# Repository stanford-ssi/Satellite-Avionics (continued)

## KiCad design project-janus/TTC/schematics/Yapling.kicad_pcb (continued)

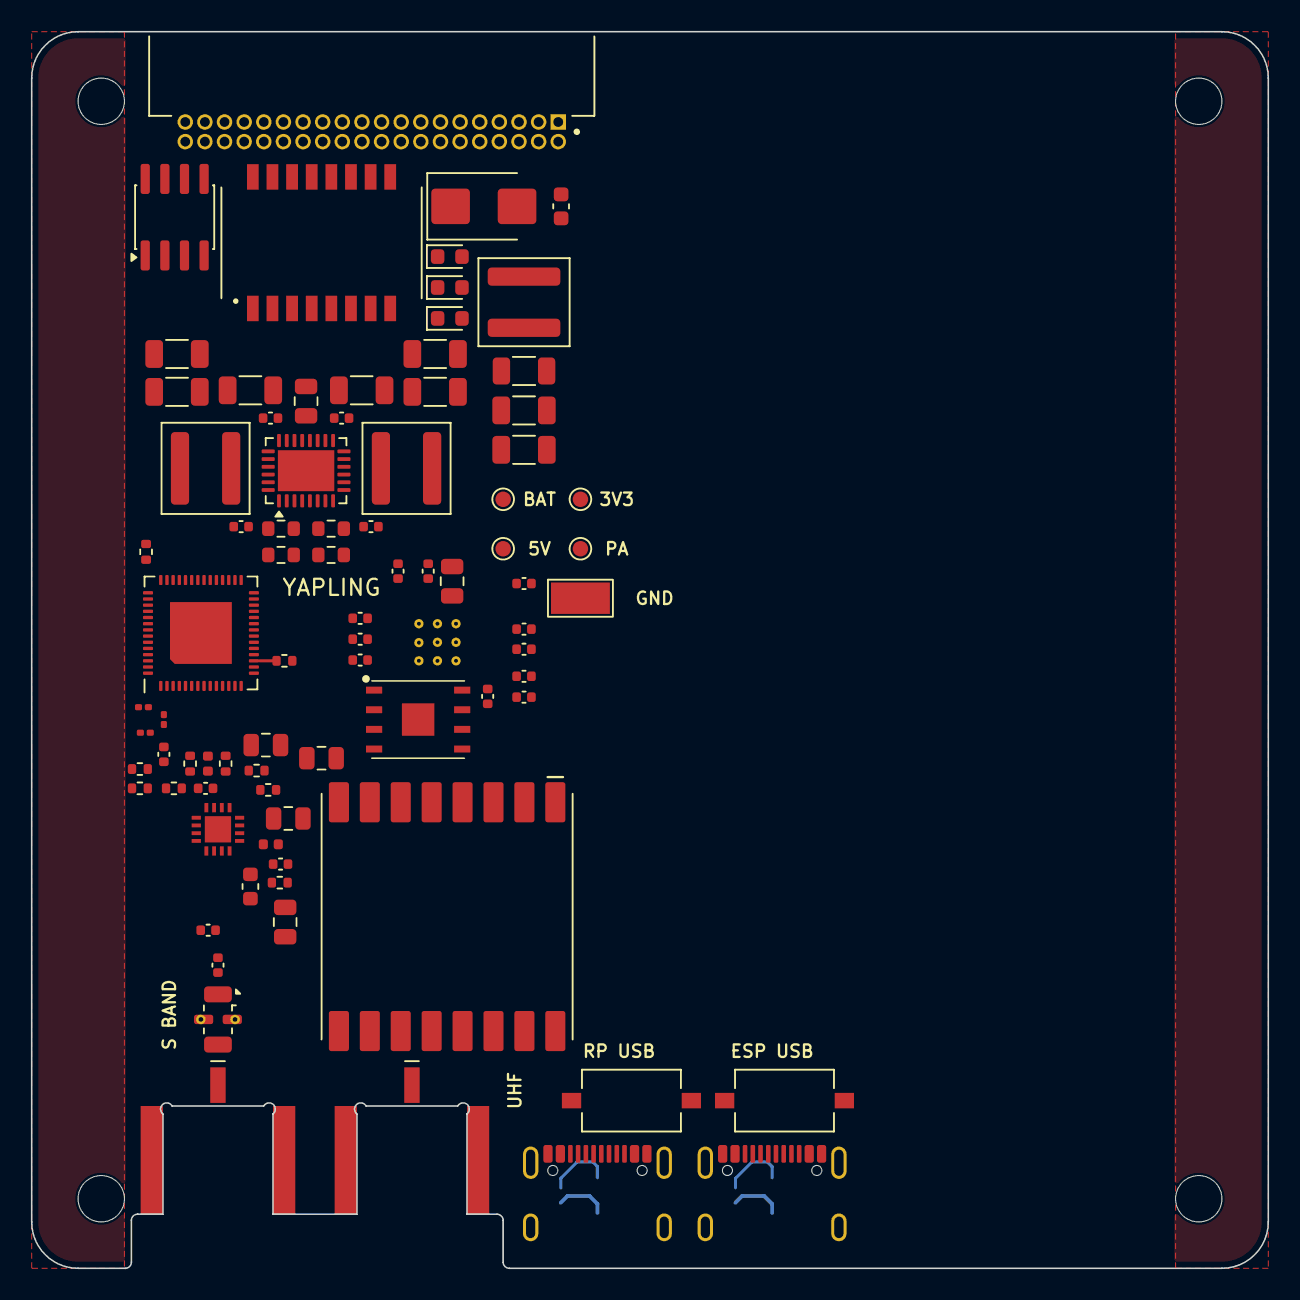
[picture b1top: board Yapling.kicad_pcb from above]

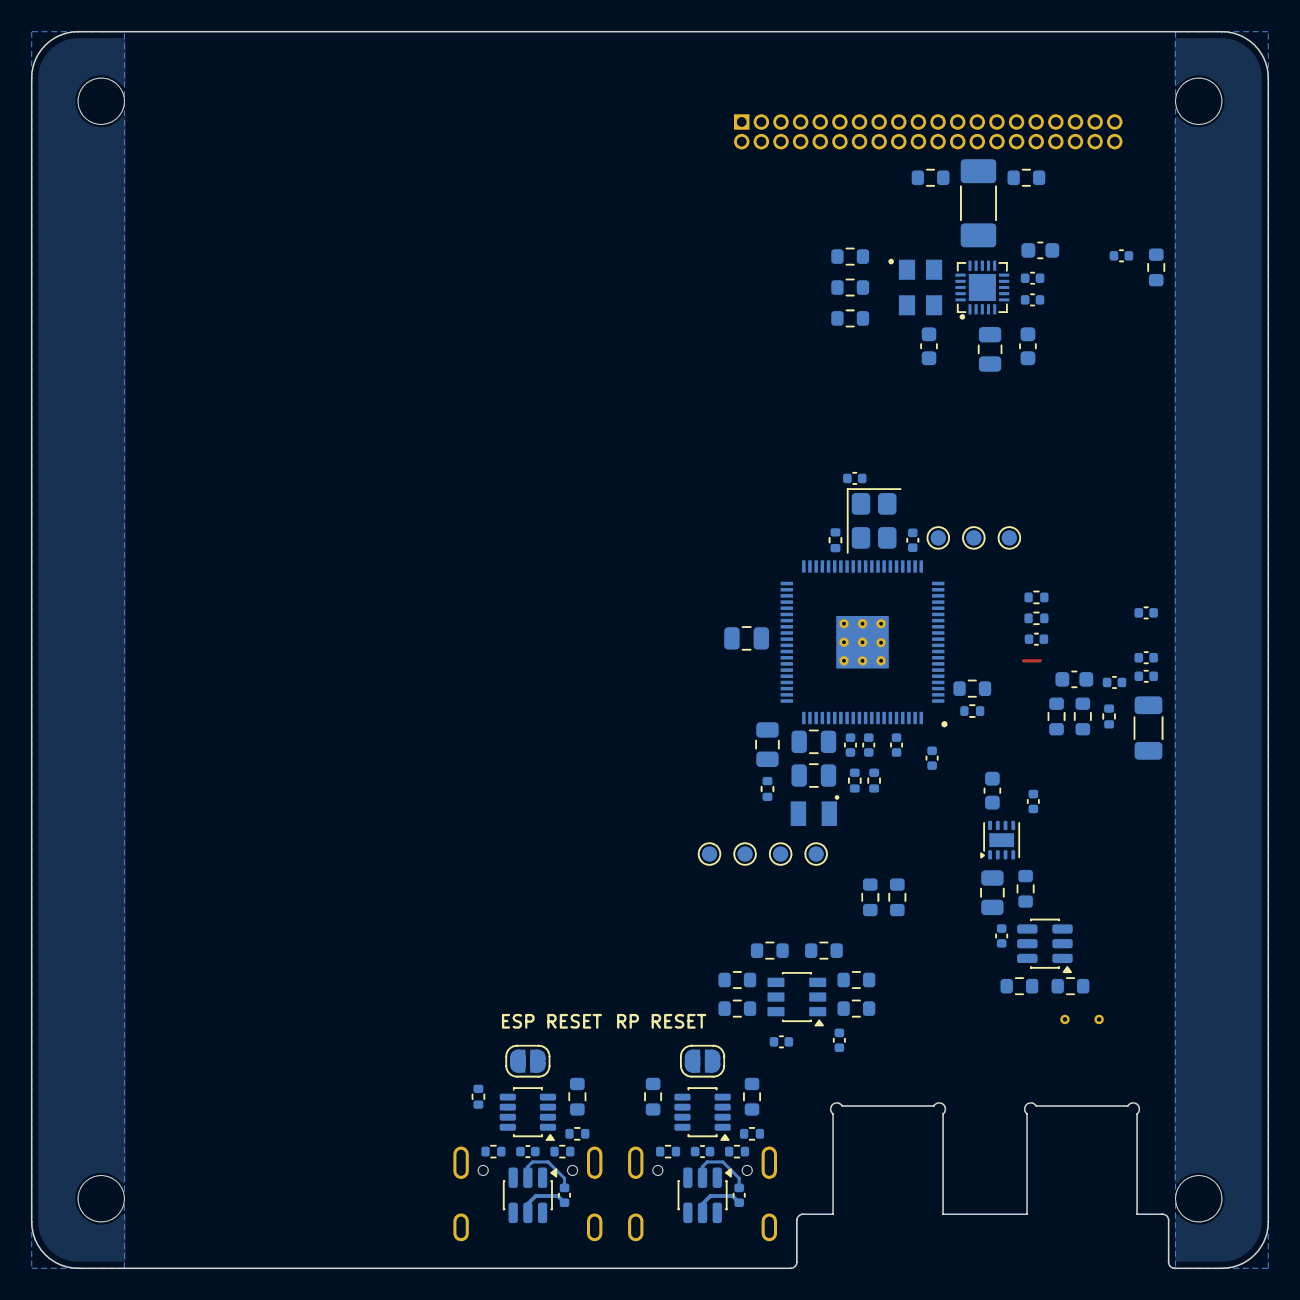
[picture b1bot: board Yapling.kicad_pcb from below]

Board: 4 copper layers, 80.0 x 80.0 mm, 182 parts (94 on the bottom side), 123 nets.

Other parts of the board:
H1, H2, H3, H4: 3 mm NPTH
MECH1: SSI P7 wedge retainers

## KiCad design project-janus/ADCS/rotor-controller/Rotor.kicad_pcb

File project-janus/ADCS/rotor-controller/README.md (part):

# Finertia

Finertia Mk 1.0 is the reaction wheel controller for the Bleps spacecraft. Its name combines the Anableps fish’s fin with the spinning rotor’s inertia. This KiCad 10 board fits the shaft face of one Faulhaber 2610T012B. Its internal rotor provides the angular momentum. Open [Rotor.kicad_pro](Rotor.kicad_pro) and follow the sheets from the spacecraft harness through CAN, control, and the three-phase bridge to the motor ribbon.

**Routed revision.** KiCad 10 found zero physical violations, zero unconnected items and zero schematic-parity issues after refilling the copper. The project also checks that track endpoints land at via centers. [Routing overview](review/Finertia-routing.png) · [Kelvin close-ups](review/Finertia-Kelvin-routing.png) · [Filled power and ground planes](review/Finertia-planes.png)

[Schematic PDF](review/Reaction-Wheel-Controller-schematic.pdf) · [Assembly STEP](review/Reaction-Wheel-Controller-assembly.step) · [Mounted assembly](review/Reaction-Wheel-Controller-assembly.png) · [Mounting profile](review/Reaction-Wheel-Controller-mounting-profile.png) · [Shaft-facing PCB](review/Reaction-Wheel-Controller-shaft-face.png) · [Motor-facing PCB](review/Reaction-Wheel-Controller-motor-face.png)

The Mk 1.0 fabrication archive includes the rear artwork and separate plated and nonplated Excellon files. [Gerbers and drill](fabrication/Finertia-Mk1.0-Gerbers-and-drill.zip) · [Decorated-board DRC](fabrication/decorated.drc.json) · [Schematic ERC](fabrication/schematic.erc.json)

The working board carries the name and service markings. At final artwork release, import the original 1,300 × 1,300 pixel *Waterline Eclipse* image onto a copy of the board. A lossless quarter-turn in the rear view brings the open water to the bottom. The import keeps the original pixels, converts the artwork to one legend ink, and clears the board openings, spacer seats, pads and lettering. The smallest engraving strokes are finer than JLCPCB’s 0.15 mm standard legend specification. Check the plotted proof with the fabricator before ordering. [Rear artwork proof](review/Finertia-rear-art-proof.png) · [Original PNG](review/art-concepts/Anableps-Waterline-Eclipse.png) · [JLCPCB legend limits](https://jlcpcb.com/capabilities/pcb-capabilities)

From the board directory, run the following with KiCad 10’s Python, Pillow, NumPy and ContourPy. Copy the schematic, project settings and libraries to a release directory and leave its Rotor.kicad_pcb path empty for the importer. Refill and check the working board, then run DRC and inspect the bottom legend Gerber on the decorated copy.

```sh
python3 artwork/apply_rear_art.py Rotor.kicad_pcb /path/to/release-copy/Rotor.kicad_pcb
```

The RP2350A firmware, SRAM programmer and CAN commissioning commands live in the project. [Build and program Finertia](firmware/PROGRAMMING.md) · [Motor control and CAN](firmware/CONTROL.md)

## Mechanical and harness interface

The 26 × 26 mm board matches the square flange with 1.5 mm corner radii. Four Ø2.2 mm nonplated PCB holes align with the motor’s Ø2.1 mm holes on a Ø30 mm circle. The Ø6.4 mm aperture gives 0.2 mm nominal radial clearance around the Ø6 mm pilot. Install four 2.5 mm-high, Ø4 mm spacers between the motor flange and PCB underside to retain the shaft datum. Use M2 through-fasteners in the flange clearance holes. The nominal 7 mm shaft projection leaves 2.9 mm above the 1.6 mm PCB. Check the actual spacer and screw dimensions, screwdriver access for the two Gecko jackscrews, ribbon strain relief and free shaft rotation before tightening. For operation in vacuum, confirm the ordered bearing lubricant. Faulhaber lists Y4192 as a separate vacuum option. [Faulhaber dimensional drawing and options](https://eshop.faulhaber.com/media/0a/d7/d4/1775629787/EN_2610_B_DFF.pdf)

| Connection | Signals in numbered order |
| --- | --- |
| J2 spacecraft, 6-way Gecko-SL | 1 protected 2S VBATT, 2 GND, 3 CAN_H, 4 regulated 3.3 V, 5 GND, 6 CAN_L |
| J3 motor ribbon | 1 phase C, 2 phase B, 3 phase A, 4 GND, 5 Hall 3.3 V, 6 Hall C, 7 Hall B, 8 Hall A |

The Mk 1.0 harness supplies separate motor and logic rails. VBATT feeds the three-phase bridge. Spacecraft 3.3 V feeds the logic, the current-sense reference and the Hall sensors. The 2610…B digital Hall supply range is 2.2–20 V. Their open-drain outputs have 3.3 kΩ pull-ups to the same 3.3 V rail. Use the six-contact Gecko-SL G125-MS10605M1R vertical plug and G125-2240696F1 cable housing. The two M2 female threads accept the cable screws on the shaft-facing side. Allow 9.95 mm above the board for the mated connector, plus wire bend and tool clearance. Each supply uses one contact. Both ground contacts are available for the return. Follow Harwin’s mating-face numbering when building this harness. [Harwin board connector](https://www.harwin.com/products/G125-MS10605M1R) · [Harwin cable housing](https://www.harwin.com/products/G125-2240696F1) · [Faulhaber AN163, table 4](https://www.faulhaber.com/fileadmin/Import/Media/AN163_EN.pdf#page=3)

Finertia uses TI’s commercial TCAN330GDCNT in SOT-23-8 on the 3.3 V logic rail. U4 pin 5 (SHDN) and pin 8 (S) are grounded for normal operation. Classical CAN stays on the same two RP2350A PIO pins and harness contacts. The earlier SSI TT&C design used SN65HVD233DR. The KiCad courtyard bounding rectangle drops from 7.40 × 5.40 mm to 4.20 × 3.60 mm, saving 24.84 mm² of bounding area. The new part specifies ±14 V bus-pin fault protection. The SN65HVD233 specifies ±36 V. Confirm this against harness fault cases. [Same-scale footprint comparison](review/Finertia-CAN-footprints.png) · [TI TCAN330G](https://www.ti.com/lit/ds/symlink/tcan330g.pdf) · [TI SN65HVD233](https://www.ti.com/lit/ds/symlink/sn65hvd233.pdf) · [SSI TT&C schematic](https://github.com/stanford-ssi/Satellite-Avionics/blob/a9a3a9240f94722b49edfb8a2d10fd50395589c4/project-janus/TTC/schematics/Backplane.kicad_sch#L2538)

OreSat’s released v5.3 solar-module PCB names TCAN330GDCNT at U1. The mission team reports that this revision operated in orbit. This is board-level flight heritage for the selected ordering code. TI sells it as a catalog part. [OreSat v5.3 board record](https://github.com/oresat/oresat-solar-hardware/blob/47d610c1964c31f049a8f9844f7881931b5d0f06/1u_panel/eagle/1u_panel.brd#L5664-L5670) · [OreSat mission status](https://www.oresat.org/technologies/cubesat-subsystems) · [TI ordering details](https://www.ti.com/product/TCAN330G/part-details/TCAN330GDCNT)

## PCB construction and assembly

All 67 populated components mount on the shaft-facing side. The motor-facing side carries the bare Tag-Connect pogo contacts and watchdog service jumper. J2 supplies 2S VBATT and 3.3 V. C24 provides 22 µF nominal on the bridge supply and C23 provides 22 µF nominal on the logic input. The motor bridge keeps its local VM ceramic and the RP2350A keeps its core regulator, inductor and bypass capacitors.

The project uses the 1.6 mm JLC06161H-2116A build with ENIG, 35 µm nominal outer copper and 15.2 µm inner copper. From L1 down, the dielectrics are 0.1164, 0.1300, 0.9328, 0.1300 and 0.1164 mm. The central dielectric consists of 0.1164 mm of 2116 prepreg, a 0.7000 mm core and a second 0.1164 mm prepreg. Select this exact stackup when ordering. [JLCPCB stackups](https://jlcpcb.com/impedance)

| Layer | Function |
| --- | --- |
| L1 / F.Cu | Components, motor bridge, Kelvin pickups, CAN pair and local ground copper |
| L2 / In1.Cu | Ground reference for L1 and L3 |
| L3 / In2.Cu | Signals, including filtered phase-current feedback |
| L4 / In3.Cu | VBATT and 3.3 V pours, plus the RP2350A core supply |
| L5 / In4.Cu | Ground reference for L6 |
| L6 / B.Cu | Motor and digital routes, ground copper and programming contacts |

Both primary ground planes form single connected copper regions. Signal tracks are restricted to L1, L3 and L6. The L2 void follows the RP2350A LX switch land and track between U1 and L1. This keeps switching-node capacitance local and leaves a continuous motor-side ground reference on L5. [RP2350 datasheet, §6.3.8.1](https://datasheets.raspberrypi.com/rp2350/rp2350-datasheet.pdf)

In a geometric width check on the refilled L4 copper with drill holes subtracted, a continuous 1.11 mm corridor reaches the motor bridge from J2, and 1.22 mm reaches the bulk capacitor C24. The 3.3 V path from J2.4 to the MCU feed at (90.76, 103.24) mm admits 0.58 mm. These are bottleneck widths around antipads in the actual pours. The two 0.40 mm links at J2.4 take the spacecraft’s 3.3 V supply directly into a pair of through-vias. All four high-gain shunt inputs stay on L1. The filtered ADC lines on L3 reference the same L2 ground as their L1 launches. The nearest ground-via distances at the ADC and filter ends are 0.59/0.63 mm on channel A and 0.60/1.09 mm on channel B, center to center. [Filled power and ground planes](review/Finertia-planes.png) · [Current-signal returns](review/Finertia-current-returns.png)

The default signal via uses a 0.20 mm hole in a 0.45 mm land. The motor-power preset uses 0.30 / 0.60 mm. The sizes are through-drilled, tented on both faces. JLCPCB’s multilayer table lists a surcharge for 0.10 or 0.15 mm holes, and for 0.20 or 0.25 mm holes with lands below 0.45 mm. The selected sizes clear those thresholds. A 0.30 mm hole in a 0.50 mm land also meets the board’s 0.10 mm annular-ring rule. [JLCPCB capabilities](https://jlcpcb.com/capabilities/Capabilities?type=1) · [JLCPCB via pricing options](https://cart.jlcpcb.com/quote?stencilLayer=6)

For the LumenPnP, the smallest passives are 0402 imperial and the new transceiver has 0.65 mm lead pitch. TI supplies TCAN330GDCNT on 8 mm tape at 4 mm pocket pitch. Opulo lists 0402 and 0.40 mm minimum lead pitch for v3 and v4. Pick the two R1/R2 pull-ups from the same 10 kΩ 0402 feeder as R5. Set the pickup nozzle and bottom-vision profile on a sample from the actual reel, and verify pin 1 against the assembly view. This dense individual board has no optical fiducials. For machine placement, add three widely spaced 1 mm copper fiducials with 2 mm mask openings on the assembly panel rails, or use a registered fixture with verified board registration. [Opulo assembly guidance](https://docs.opulo.io/guides/design-for-lumenpnp/) · [TI device and tape drawing](https://www.ti.com/lit/ds/symlink/tcan330g.pdf)

From the board directory, this exports the 67 top-side placements in KiCad’s ASCII .pos format for OpenPnP. Generate the file from the same revision used for the fabrication drawings.

```sh
kicad-cli pcb export pos --side front --smd-only --exclude-dnp --units mm --format ascii -o Finertia-top.pos Rotor.kicad_pcb
```

The rear legend clears the Tag-Connect pattern, the watchdog jumper and its WD label. The three guide holes maintain at least 0.277 mm nominal clearance to front copper. Each of the two watchdog lands measures 0.55 × 0.75 mm, with a 0.25 mm gap. The WD legend is condensed to keep the board’s nominal 1.0 mm text height. Program and remove the temporary solder bridge before mounting the controller.

Install the KiCad 10 standard 3D model libraries for the native viewer. The project includes additional models for the Faulhaber motor, spacers, Gecko and custom packages. The Gecko model represents the unmated connector envelope. The standalone assembly STEP includes the populated PCB, spacers and motor.

## Copper and placement

U7 is the DRV8311P-Q1 bridge. U8 and U9 are the INA241A3-Q1 phase-current amplifiers. J1 is SWD, J2 is the harness and J3 is the motor ribbon. The reference numbers run from 1 within each part prefix. [Reference conversion table](review/Finertia-reference-map.csv) · [Component-side placement](review/Finertia-placement.png)

The routing review compares all 50 routed nets with revision `1a80902`. Lengths are planar track totals. The switching-copper comparison counts same-layer runs within a 0.50 mm edge gap and 15° of parallel. The reference-plane check projects signal centerlines onto L2 or L5 and excludes their own via clearances. [Per-net routing comparison](review/Finertia-routing-comparison.csv)

The two-terminal 0.100 Ω WSL0603 shunts each have separate motor-current and sense paths. Motor current enters and leaves on the wide copper. Each 0.15 mm sense lead contacts an inside corner of its own termination and continues on L1 to its INA241 input. R20 sits directly over U8. Moving it there reduced each phase-A sense lead from 2.396 to 1.856 mm and increased the U7-to-shunt force path from 9.17 to 13.04 copper squares. The A− lead clears the annulus of the separate motor-current via by 0.195 mm. The dimensions below are nominal CAD centerlines. The exposed length excludes the portions under the shunt and amplifier lands. [Kelvin detail](review/Finertia-Kelvin-routing.png) · [TI INA241 layout](https://www.ti.com/lit/ds/symlink/ina241a-q1.pdf) · [Vishay WSL shunts](https://www.vishay.com/docs/30100/wsl.pdf)

| Channel | IN+ | IN− | Each pickup to input-pad center | Exposed length difference |
| --- | --- | --- | ---: | ---: |
| Phase A | R20.1 → U8.8 | R20.2 → U8.1 | 1.856 mm | 0.000 mm |
| Phase B | R21.1 → U9.8 | R21.2 → U9.1 | 1.908 mm | <0.001 mm |

The OUTA route leaves U7 at 0.30 mm, narrows to 0.19 mm between neighboring lands and returns to 0.30 mm at R20. The OUTB escape widens from 0.18 to 0.30 mm. C25.1 reaches its VM via through a straight 0.70 mm long, 0.42 mm wide connection. The charge-pump capacitor C27 and VM bypass C25 stay on the component side beside U7. For the two precision channels, GP26 and GP27 each have a local ADC filter capacitor. The integrated phase-C monitor also connects to GP28. Offset, PWM settling and current-sampling accuracy still require bench measurement. [TI DRV8311-Q1 layout guidance](https://www.ti.com/lit/ds/symlink/drv8311-q1.pdf)

Hall C leaves J3.6 on L1, then uses L3 to cross the L6 motor-phase route with L5 ground between them. This removes the previous 1.35 mm same-layer parallel run within 0.50 mm of phase C. The minimum same-layer copper separation increased from 0.145 to 0.325 mm, including via lands. The nearest ground stitches to the connector-side and added Hall vias are 0.63 and 1.13 mm away, center to center. The filtered phase-B current signal now runs parallel to the MRAM clock for 0.46 mm within a 0.50 mm edge gap. During bring-up, scope Hall C at U1.16 and check for extra edges during drive and braking. [Hall C routing comparison](review/Finertia-Hall-C-routing.png)

The CAN bus pair runs from J2.3/J2.6 to U4.7/U4.6 entirely on L1 over L2 ground. Both the straight and diagonal coupled sections use 0.115 mm conductors with a 0.395 mm edge gap. The nominal setback to the L1 ground pour is 0.40 mm. The connector contacts set the wider spacing at the harness end. A 2-D quasi-static model predicts about 119 Ω for the uniform section, using the 2116 prepreg thickness, εr = 4.16 and JLCPCB’s published etch and soldermask assumptions. Pads, tolerance and the contact breakouts affect the assembled path. Use a 120 Ω twisted-pair harness with termination at the two physical bus ends. [Reproduce the cross-section estimate](review/can_impedance.py) · [JLCPCB calculator parameters](https://jlcpcb.com/help/article/user-guide-to-the-jlcpcb-impedance-calculator) · [TI TCAN330G](https://www.ti.com/lit/ds/symlink/tcan330g.pdf)

TraceMaker 0.12.1 routed the local U4 CAN-TX pull-up and U6 watchdog-enable pull-up branches. Together these use eight component-side segments and zero vias. The CAN-TX route goes from U4.1 to R5.2. The watchdog route goes from U6.6 to R8.2. For repeat trials, all other copper was locked, and the plane layers were excluded. On the four longer housekeeping nets, the selected-net trials left all six requested connections open. The committed longer routes use fixed pin escapes and grid-based search, followed by KiCad geometry and connectivity checks. [CAN and watchdog close-up](review/Finertia-CAN-watchdog.png) · [TraceMaker routing implementation](https://dingooz.github.io/TraceMaker/dev/05-routing/)

The RP2350A buck regulator uses the marked Abracon 3.3 µH inductor. Its marked terminal faces VCORE, matching Raspberry Pi’s RP2350A Minimal R4 placement. C5 and C6 sit between U1 and L1 with their ground lands 0.85 mm apart. Their switching current returns directly to U1.47 on top copper. This copper connects to the ground plane through two adjacent vias spaced 0.66 mm apart. C7 has a separate 0.71 mm ground connection to its own via. The feedback trace starts at C6’s output land. The 2.55 mm R4-to-C7 filtered supply stays on top, clear of the LX opening in L2. Its closest copper edge is 0.30 mm from LX. The LX path measures 4.17 mm from pad center to pad center. [Regulator layout comparison](review/Finertia-core-regulator.png) · [RP2350 datasheet, §6.3.8](https://datasheets.raspberrypi.com/rp2350/rp2350-datasheet.pdf) · [RP2350 hardware design guide](https://pip-assets.raspberrypi.com/categories/1214-rp2350/documents/RP-008280-DS-2-hardware-design-with-rp2350.pdf) · [Abracon package drawing](https://abracon.com/datasheets/AOTA-B201610S3R3-101-T.pdf#page=4)

C5 and C6 use the 4.7 µF Murata part fitted on Raspberry Pi’s Minimal R4. Their copper lands measure 0.45 × 0.55 mm with a 0.50 mm gap. At 25 °C and 10 mV RMS, Murata’s typical model gives 1.53 µF at 3.3 V and 3.28 µF at 1.1 V. On first hardware, probe directly across C6 with a ground spring. Record core startup, steady ripple, and overshoot and undershoot when the MCU enters and exits a heavy load, at the intended supply and temperature limits. Check the southwest M2 fastener and spacer against L1 during assembly. [Murata land dimensions, table 2](https://www.icbanq.com/icdownload/V2_DATA/ICBShop/Board/Murata/GRM155R60J475ME47-01A.pdf#page=26) · [Murata DC-bias model](https://ds.murata.com/simsurfing/mlcc.html?partnumbers=%5B%22GRM155R60J475ME47%22%5D&oripartnumbers=%5B%22GRM155R60J475ME47D%22%5D&lcid=en-us)

The pin numbers above the MCU sheet’s capacitor banks identify the intended bypass. All twelve assigned supply capacitors connect locally to U1. C11 and C12 share a ground via between the two parts. C18 uses the same 4.7 µF 0402 part as C6. [RP2350 hardware design guide](https://datasheets.raspberrypi.com/rp2350/hardware-design-with-rp2350.pdf)

| RP2350A supply | Pin → bypass capacitor, center spacing |
| --- | --- |
| IOVDD | 1 → C8 (2.20 mm), 11 → C9 (2.56 mm), 20 → C10 (1.64 mm) |
| IOVDD | 30 → C11 (2.46 mm), 38 → C12 (3.13 mm), 45 → C13 (4.27 mm) and adjacent C14 (2.53 mm) |
| ADC, OTP and QSPI | 44 → C14 (2.88 mm), 53 → C15 (2.55 mm), 54 → C16 (3.47 mm) |
| DVDD | 6 → C17 (1.99 mm), 23 → C18 (1.88 mm), 39 → C19 (1.65 mm) |

## Bench bring-up

1. **Verify power and recovery.** With the bridge asleep, verify spacecraft 3.3 V at J1.1 and between J3.5 and J3.4, then verify VBATT at C24. Exercise both rail startup orders and loss of each rail. Verify that MCU reset and logic-rail loss pull U7 nSLEEP low and leave the phase outputs high impedance. R9 holds nSLEEP low through 3.3 kΩ. On RP2350 A2 keep the GP21 input buffer disabled when using it as an output and scope nSLEEP through reset. Check the loaded logic rail against the RP2350’s 3.135 V analog-supply minimum. U3 trips at 3.08 V nominal, so a slow sag can cross that supply limit before reset. Confirm the EPS rail tolerance and shutdown behavior. Probe RUN_N at J1.3 during a slow power ramp and a watchdog reset. Program the bare board through rear J1 before installing the motor. Use a Tag-Connect TC2030-CTX-NL cable with normal Cortex-10 orientation. J1 pins 1–6 are 3.3 V VTref, SWDIO, RUN_N, SWCLK, GND and unused SWO. Bridge the normally open rear JP1 (marked WD) while power is off to inhibit the external watchdog. Clear the bridge and verify JP1 is open before operation. For the running watchdog, provide falling WDI edges within the 1.44 s minimum timeout. Stop servicing WDI and verify the nominal 200 ms reset pulse and return to bridge sleep. [TPS3435-Q1 timing](https://www.ti.com/lit/ds/symlink/tps3435-q1.pdf) · [Tag-Connect cable](https://www.tag-connect.com/product/tc2030-ctx-nl-6-pin-no-legs-cable-with-10-pin-micro-connector-for-cortex-processors) · [Target land pattern](https://www.tag-connect.com/wp-content/uploads/bsk-pdf-manager/2019/12/TC2030-IDC-NL-Datasheet-Rev-B.pdf)
2. **Validate boot with the motor installed.** Fit the image in 512 KiB and put a bootable IMAGE_DEF in the first 4 KiB. A writer running from SRAM can issue WREN (06h), WRITE (02h) and READ (03h) to verify the image. Configure QMI for 03h single-SPI reads with 24-bit addresses. Set a conservative flash clock divider from SRAM before increasing the system clock and follow the RP2350 QMI clock-change sequence. Verify SCK ≤40 MHz, CS high ≥40 ns, setup and hold ≥10 ns, and first CS low ≥400 µs after the MRAM reaches 3.0 V. Exercise cold power-up, brownout and watchdog restart. Measure three-axis field magnitude at the U2 site through one revolution, first unpowered and then under load. Everspin’s read/standby and write absolute maximum is 12,000 A/m, approximately 15.1 mT in air. Confirm margin including probe uncertainty before relying on direct MRAM boot. [RP2350 §5.2.7](https://pip-assets.raspberrypi.com/categories/1214-rp2350/documents/RP-008373-DS-4-rp2350-datasheet.pdf) · [Everspin tables 6, 12 and 14](https://www.everspin.com/sites/default/files/EST00459_MR2xH40_Datasheet_Rev12.6_08092020.pdf)
3. **Establish commutation.** Turn the shaft by hand, log all six legal Hall states in both directions, and measure phase order and electrical zero. Estimate rotor angle between Hall edges and define startup and reversal behavior at low speed. Wake U7, wait 3 ms and use SPI mode 1 with parity. Start with 40 kHz center-aligned PWM for the low-inductance winding. Use GP20 as the carrier reference with PWM_OSC_SYNC = 2h. A 64-clock three-duty write at 5 MHz takes 12.8 µs of the 25 µs carrier period. The supplied firmware runs the current loop at 5 kHz, once every eight carrier periods. Scope when the new duties take effect, find a settled interval for both ADC samples, and verify ripple and winding temperature. Sample GP26 and GP27 after PWM common-mode transients settle, account for conversion skew, and reconstruct phase C as −(A+B). Calibrate polarity, zero and gain against independent bidirectional phase-current references before closing the loop. GP28 provides an integrated phase C cross-check when its low-side FET conducts. Enable the integrated amplifier and measure its zero with the rotor stationary and all low-side FETs on. [Faulhaber Hall sequence](https://www.faulhaber.com/fileadmin/Import/Media/AN163_EN.pdf) · [Faulhaber PWM guidance](https://www.faulhaber.com/fileadmin/Import/Media/AN190_EN.pdf#page=3) · [DRV8311-Q1 PWM synchronization, current sensing and tSPI](https://www.ti.com/lit/ds/symlink/drv8311-q1.pdf)
4. **Exercise the vehicle interface.** Drive Classical CAN through PIO on GP2 TX and GP3 RX. Match the vehicle bitrate, terminate the two bus ends, and verify bidirectional traffic, arbitration, bus-off recovery and bridge behavior after command loss. Read TMP100-Q1 at 7-bit I²C address 0x48. Its measurement is local PCB temperature. The motor’s 177 mA DC-equivalent continuous rating assumes 22 °C ambient and the catalog thermal mounting condition. Qualify the phase-current limit from measured winding temperature on the assembled motor. The winding limit is 80 °C. [TCAN330G](https://www.ti.com/product/TCAN330G) · [Faulhaber motor ratings](https://eshop.faulhaber.com/media/0a/d7/d4/1775629787/EN_2610_B_DFF.pdf)

## Slew torque and phase-current sensitivity

The 2 kg Bleps cavity model has a largest principal inertia of 0.00496250 kg·m². From a standstill, one wheel on that axis must exchange 86.6 µN·m·s to reach 1°/s or 173.2 µN·m·s to reach 2°/s. The bare rotor needs speed changes of approximately 1,047 and 2,094 rpm. The table shows the acceleration component of current using the catalog torque constant of 17.6 mN·m/A. Add bearing losses, external torque and commutation error as applicable. [Faulhaber 2610T012B motor constants](https://eshop.faulhaber.com/en/2610T012B/2610T012B)

| Time to reach rate | 1°/s, DC equivalent | 2°/s, DC equivalent |
| --- | ---: | ---: |
| 0.1 s | 49.2 mA | 98.4 mA |
| 1 s | 4.92 mA | 9.84 mA |
| 2 s | 2.46 mA | 4.92 mA |

Faulhaber defines catalog BLDC current as DC-equivalent. For sinusoidal commutation, multiply by about 1.10 for phase peak or 0.78 for phase RMS. With amplitude-invariant Park scaling and zero d-axis current, q-axis current equals phase peak and the modeled torque constant is about 16.0 mN·m/A of q-axis current. The catalog 177 mA continuous rating corresponds to about 195 mA peak and 138 mA RMS. Measure shaft torque against commanded q-axis current and qualify the winding limit under the actual mounting and ambient conditions. The bridge's ampere-scale overcurrent protection protects the power stage. Apply separate phase-current and thermal limits in firmware. [Faulhaber AN183, p. 12](https://www.faulhaber.com/fileadmin/Import/Media/AN183_EN.pdf#page=12) · [Faulhaber AN190, p. 4](https://www.faulhaber.com/fileadmin/Import/Media/AN190_EN.pdf#page=4) · [TI DRV8311-Q1 electrical characteristics](https://www.ti.com/lit/ds/symlink/drv8311-q1.pdf)

The supplied 8.2 V simulation estimates 61 ms to acquire 2°/s and about 3.04 mA to sustain the rotor at 2,094 rpm against drag. Interpreted as catalog DC-equivalent current, the latter corresponds to about 3.34 mA sinusoidal phase peak and a 16.7 mV peak signal at the current amplifier. Validate both operating points on the bench.

The two inline INA241A3-Q1 channels use 0.100 Ω shunts and gain of 50 V/V, giving 5 mV/mA about midrail. Each amplifier reads its shunt over a dedicated Kelvin pair. The amplifier’s maximum 10 µV input offset at 25 °C under specified conditions is equivalent to 0.10 mA. At 3.3 V, the ideal 12-bit ADC step is 0.806 mV or 0.161 mA. Sweep known currents in both directions, including the 3 mA region, and log both sequential ADC samples, PWM timing, Hall angle, estimated q-axis current, speed and temperature. Check warm offset, noise and ripple at the chosen loop bandwidth during acquisition, steady rotation and reversal. Compare measured error to the allocated pointing and jitter budget. A provisional 10% budget at 3 mA DC-equivalent is about 5.3 µN·m. [TI INA241A-Q1](https://www.ti.com/product/INA241A-Q1) · [RP2350 ADC](https://datasheets.raspberrypi.com/rp2350/rp2350-datasheet.pdf)

## Motor winding choice

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
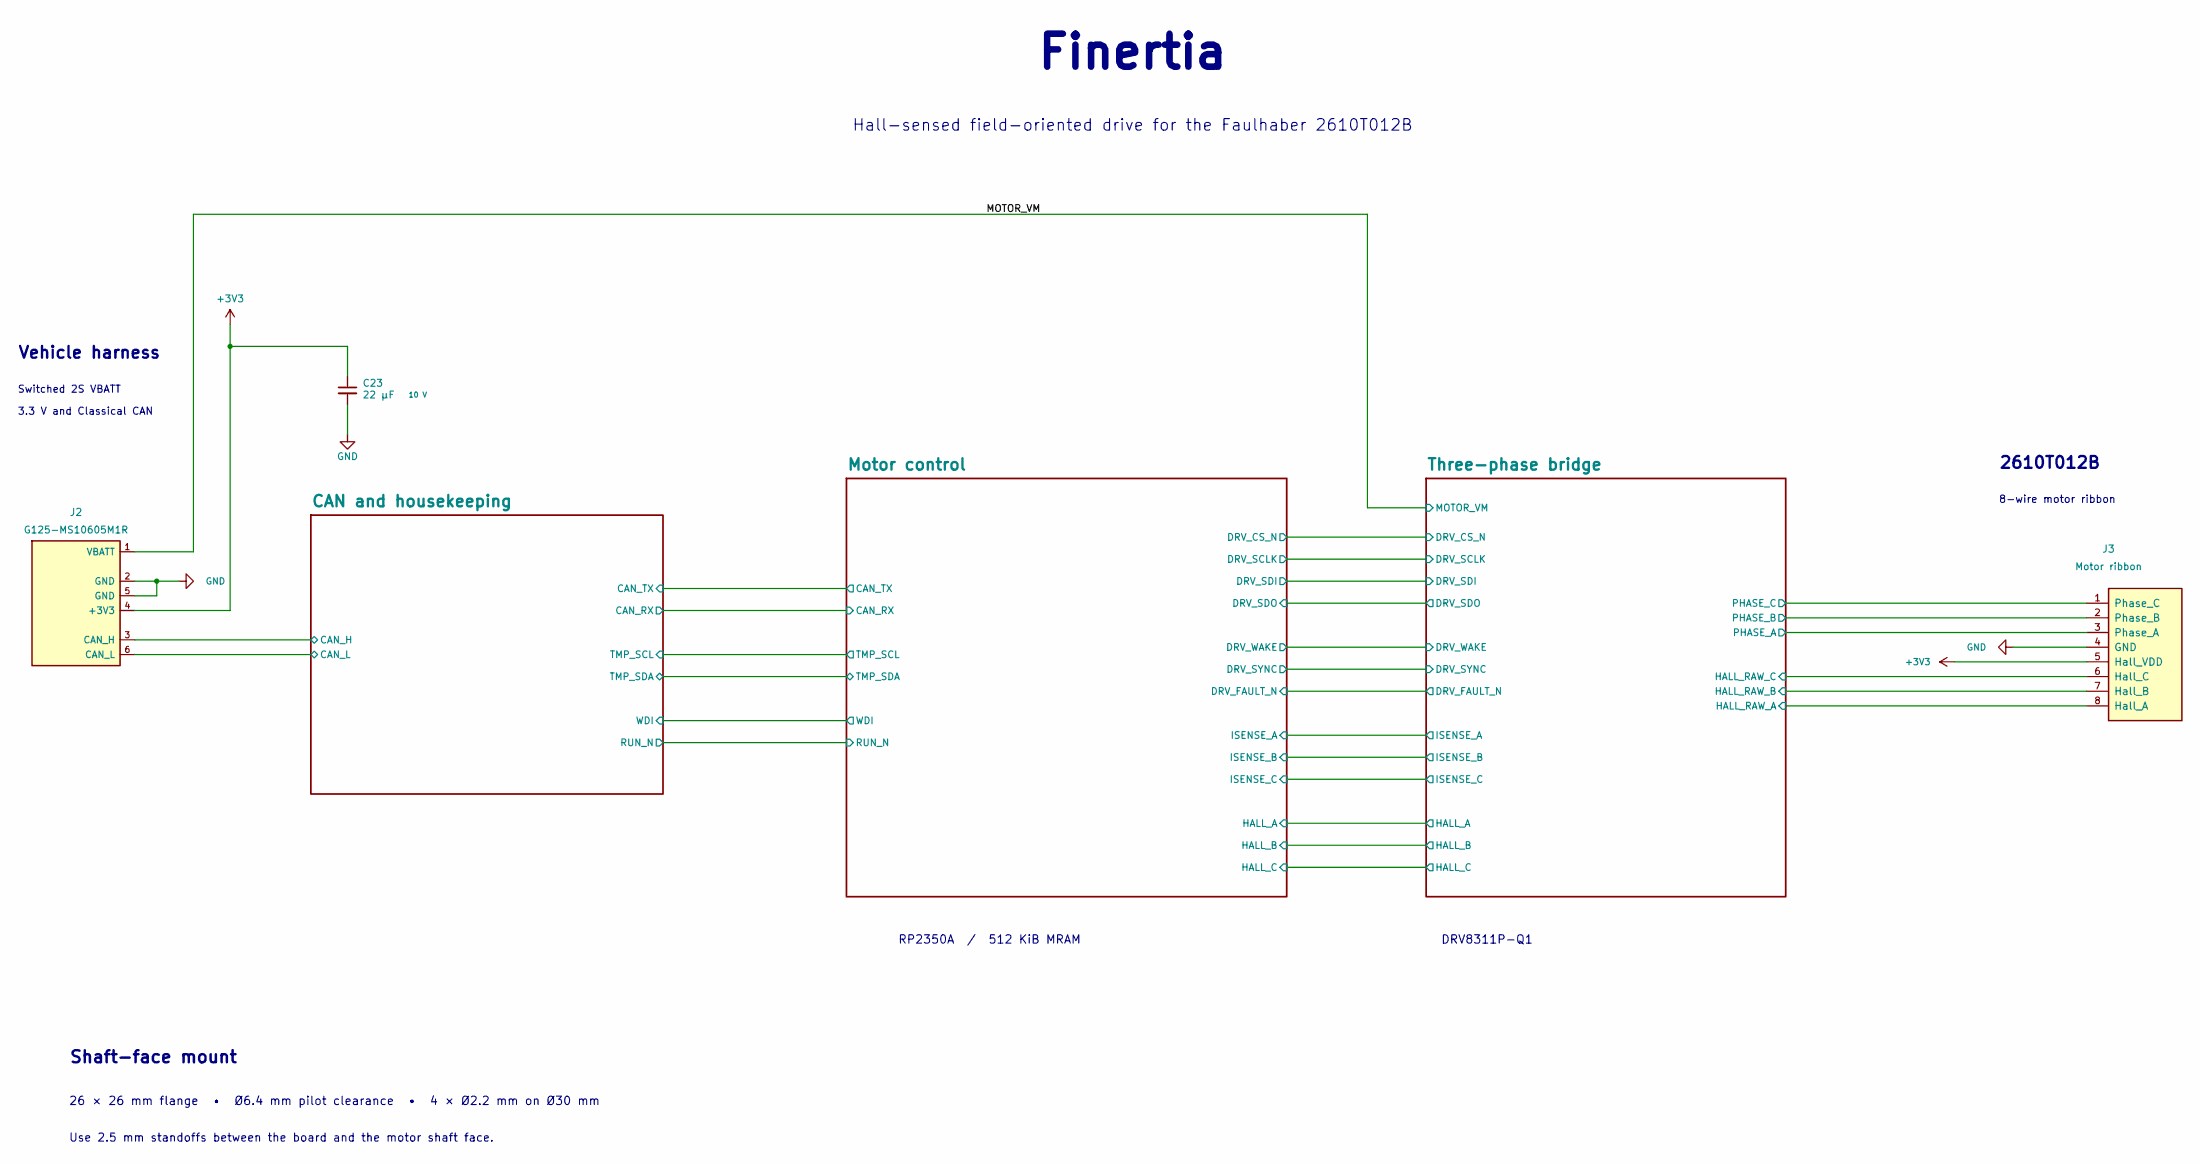
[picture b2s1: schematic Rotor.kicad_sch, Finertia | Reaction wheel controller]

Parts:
C23: 22 µF; Murata_GRM21_2012_Reflow; Voltage 10 V; MPN GRM21BR61A226ME44L
J2: G125-MS10605M1R; MPN G125-MS10605M1R
J3: Motor ribbon; Faulhaber_2610_Ribbon_1x08_P1.00mm

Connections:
+3V3: C23.1, J2.4 (+3V3), J3.5 (Hall_VDD); also elsewhere on the board
/CAN and housekeeping/CAN_H: J2.3 (CAN_H); also elsewhere on the board
/CAN and housekeeping/CAN_L: J2.6 (CAN_L); also elsewhere on the board
/MOTOR_VM: J2.1 (VBATT); also elsewhere on the board
/Three-phase bridge/HALL_RAW_A: J3.8 (Hall_A); also elsewhere on the board
/Three-phase bridge/HALL_RAW_B: J3.7 (Hall_B); also elsewhere on the board
/Three-phase bridge/HALL_RAW_C: J3.6 (Hall_C); also elsewhere on the board
/Three-phase bridge/PHASE_A: J3.3 (Phase_A); also elsewhere on the board
/Three-phase bridge/PHASE_B: J3.2 (Phase_B); also elsewhere on the board
/Three-phase bridge/PHASE_C: J3.1 (Phase_C); also elsewhere on the board
GND: C23.2, J2.2 (GND), J2.5 (GND), J3.4 (GND); also elsewhere on the board

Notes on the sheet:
Use 2.5 mm standoffs between the board and the motor shaft face.
Finertia
Hall-sensed field-oriented drive for the Faulhaber 2610T012B
3.3 V and Classical CAN
Switched 2S VBATT
DRV8311P-Q1
Vehicle harness
Shaft-face mount
RP2350A / 512 KiB MRAM
8-wire motor ribbon
2610T012B
26 × 26 mm flange • Ø6.4 mm pilot clearance • 4 × Ø2.2 mm on Ø30 mm

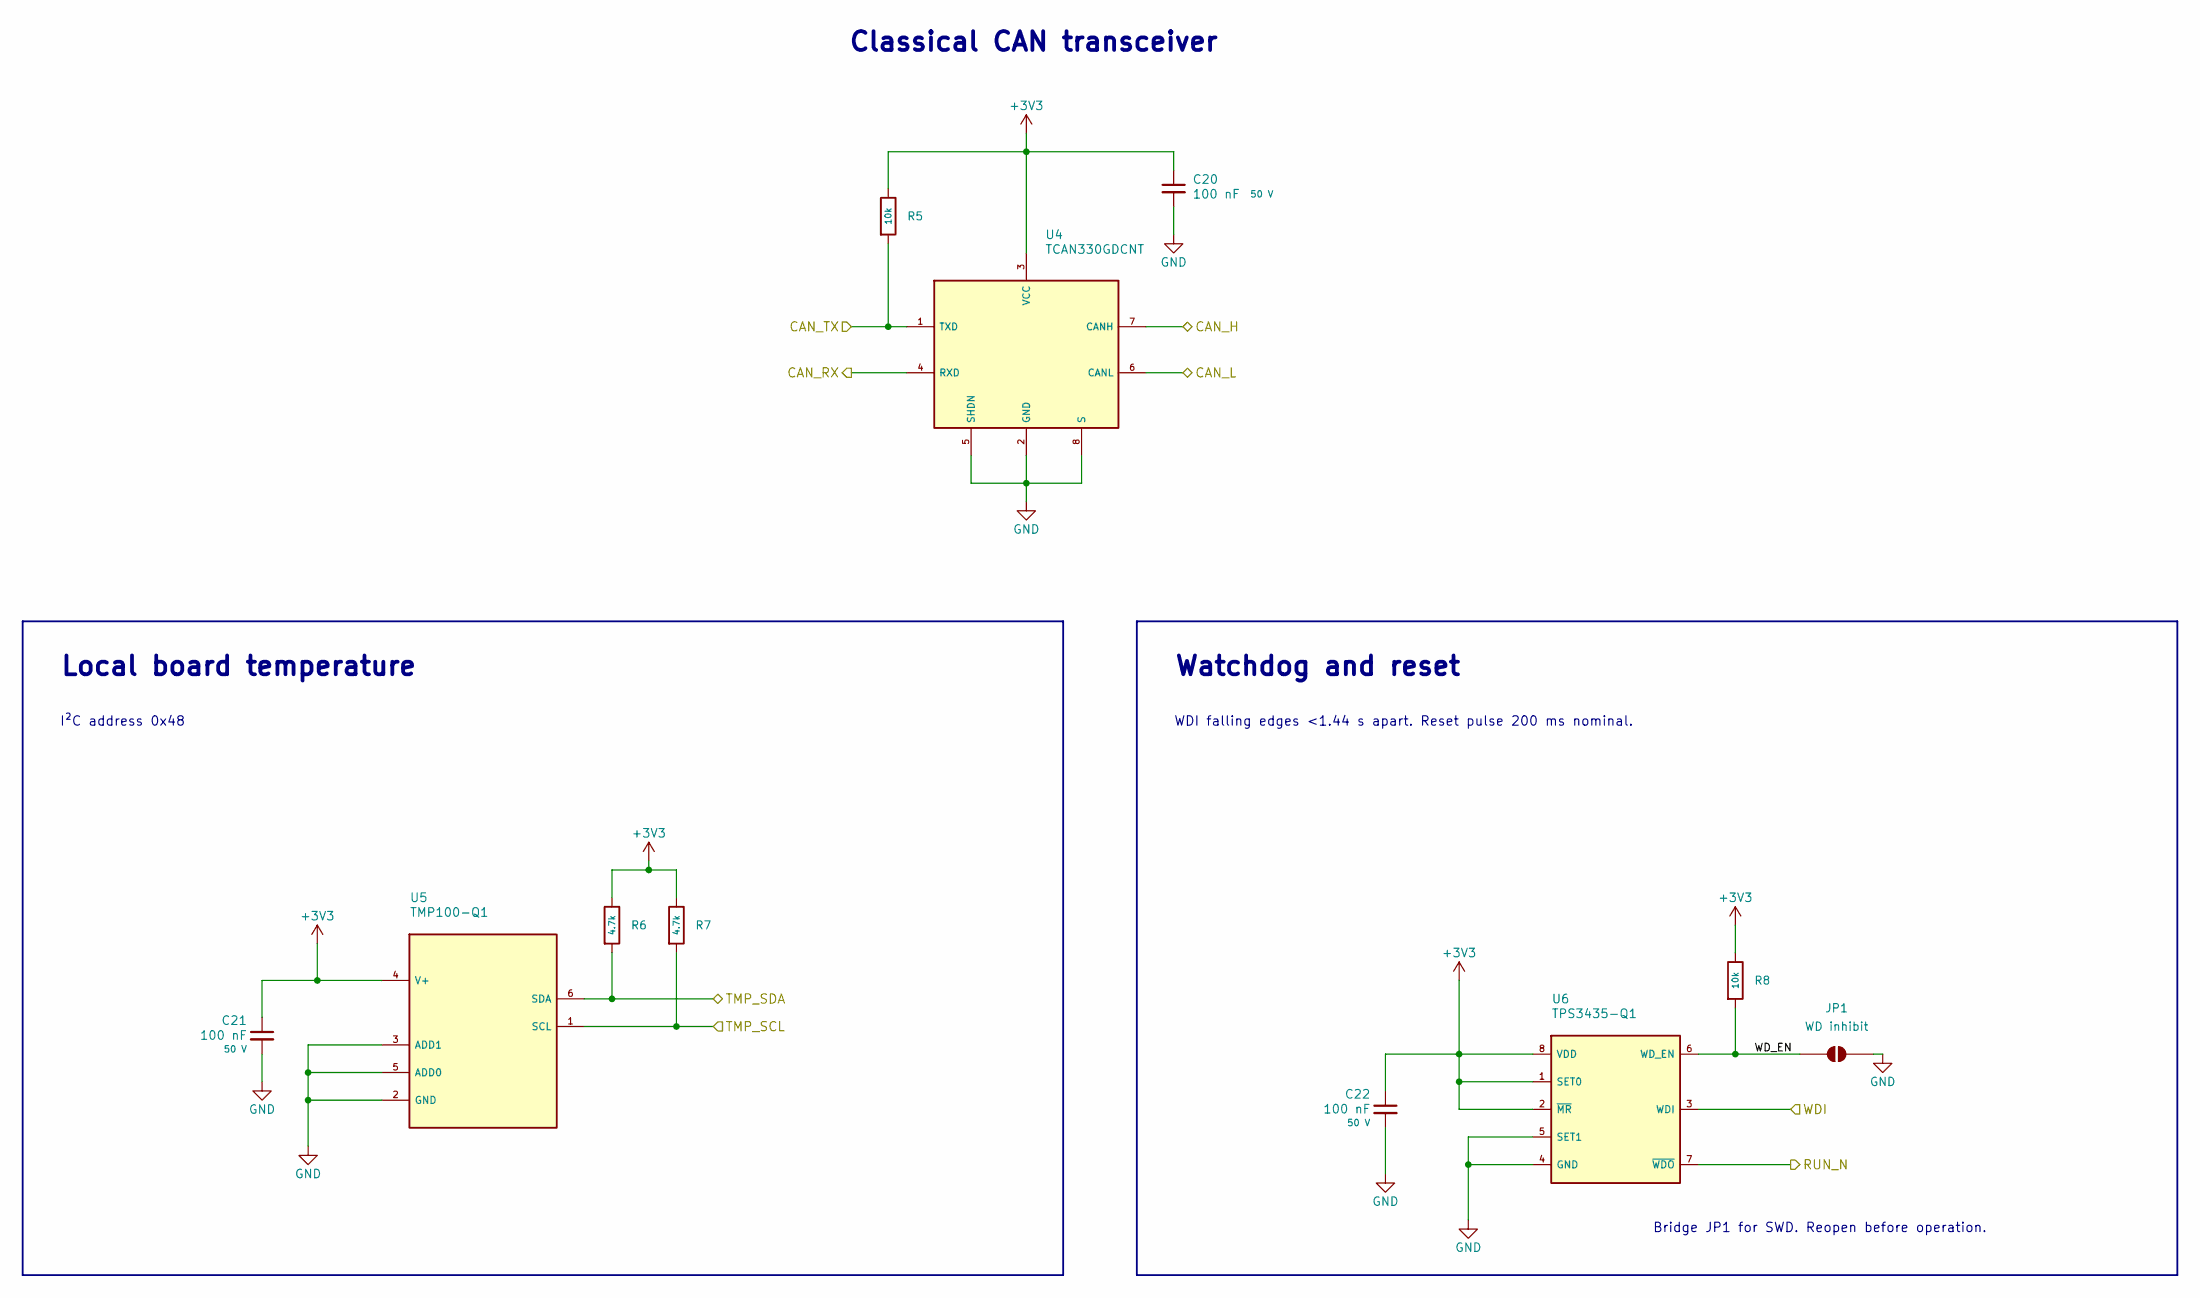
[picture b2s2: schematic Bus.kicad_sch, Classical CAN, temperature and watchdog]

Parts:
C20, C21, C22: 100 nF; C_0402_1005Metric; Voltage 50 V; MPN GCM155R71H104KE02D
JP1: WD inhibit; WD-Bridge_1.35x0.75mm
R5, R8: 10k; R_0402_1005Metric; MPN CRCW040210K0FKED
R6, R7: 4.7k; R_0402_1005Metric; MPN CRCW04024K70FKED
U4: TCAN330GDCNT; TI_DCN0008A_SOT-23-8_2.9x1.6mm_P0.65mm; MPN TCAN330GDCNT
U5: TMP100-Q1; TI_DBV0006A_SOT-23-6; MPN TMP100AQDBVRQ1
U6: TPS3435-Q1; TPS3435_DDF; MPN TPS3435CAKAGDDFRQ1

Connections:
+3V3: C20.1, C21.1, C22.1, R5.1, R6.1, R7.1, R8.1, U4.3 (VCC), U5.4 (V+), U6.1 (SET0), U6.2 (~MR), U6.8 (VDD); also elsewhere on the board
/CAN and housekeeping/CAN_H: U4.7 (CANH); also elsewhere on the board
/CAN and housekeeping/CAN_L: U4.6 (CANL); also elsewhere on the board
/CAN and housekeeping/CAN_RX: U4.4 (RXD); also elsewhere on the board
/CAN and housekeeping/CAN_TX: R5.2, U4.1 (TXD); also elsewhere on the board
/CAN and housekeeping/TMP_SCL: R7.2, U5.1 (SCL); also elsewhere on the board
/CAN and housekeeping/TMP_SDA: R6.2, U5.6 (SDA); also elsewhere on the board
/CAN and housekeeping/WDI: U6.3 (WDI); also elsewhere on the board
/CAN and housekeeping/WD_EN: JP1.1 (A), R8.2, U6.6 (WD_EN)
/Motor control/RUN_N: U6.7 (~WDO); also elsewhere on the board
GND: C20.2, C21.2, C22.2, JP1.2 (B), U4.2 (GND), U4.5 (SHDN), U4.8 (S), U5.2 (GND), U5.3 (ADD1), U5.5 (ADD0), U6.4 (GND), U6.5 (SET1); also elsewhere on the board

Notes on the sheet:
Classical CAN transceiver
WDI falling edges <1.44 s apart. Reset pulse 200 ms nominal.
Local board temperature
Bridge JP1 for SWD. Reopen before operation.
Watchdog and reset
I²C address 0x48

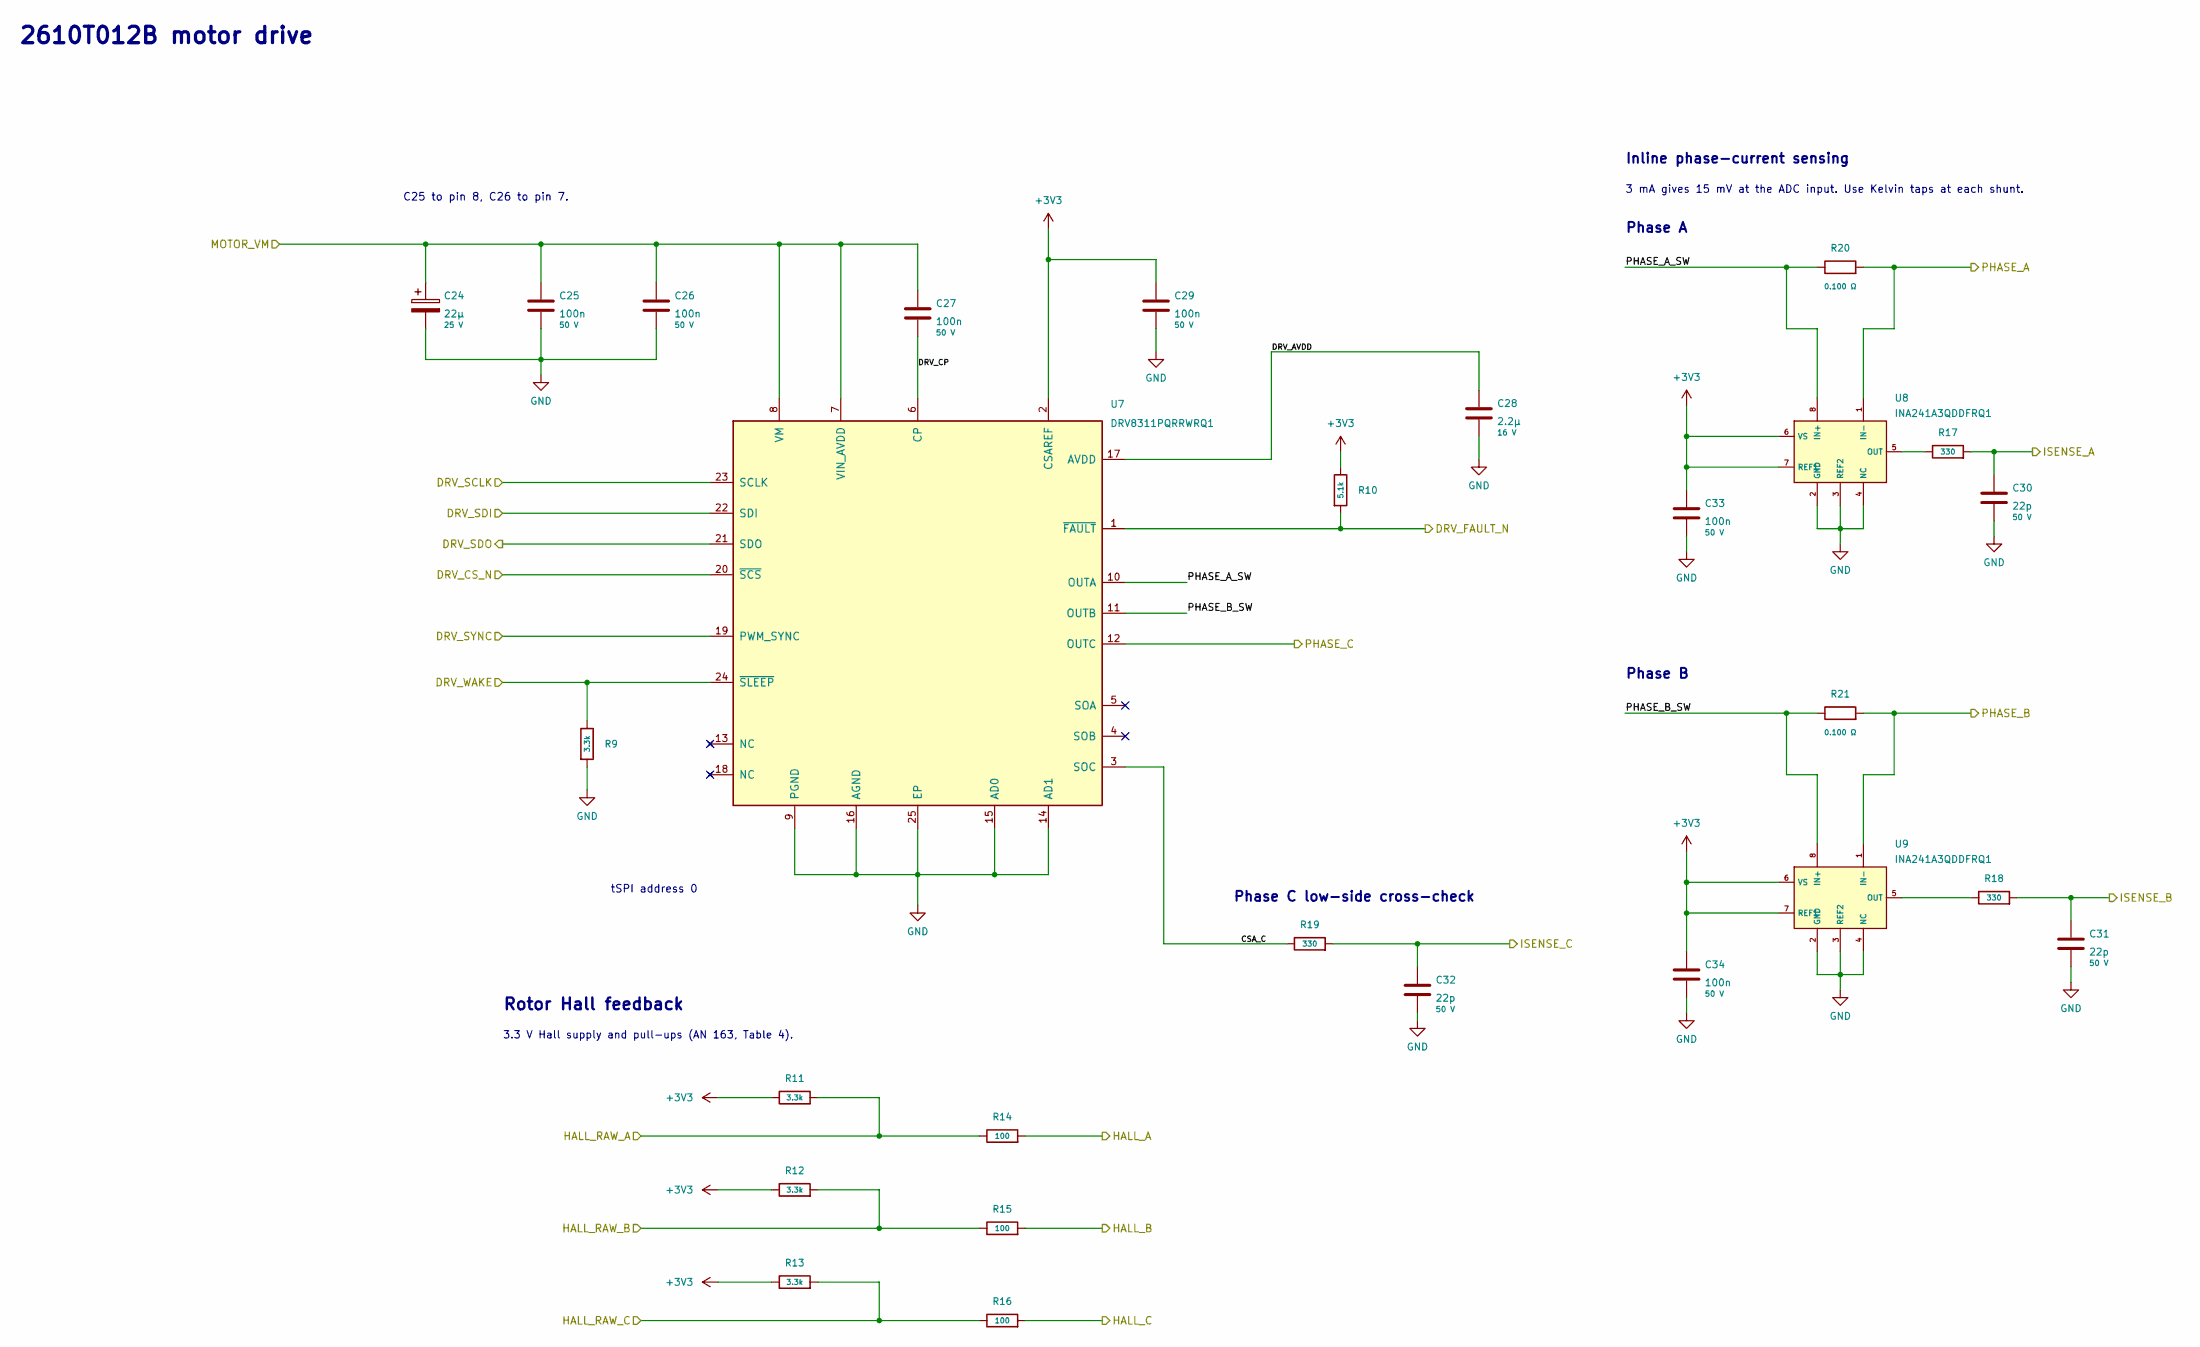
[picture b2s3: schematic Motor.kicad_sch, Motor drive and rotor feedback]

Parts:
C24: 22µ; KEMET_T521_3528_B_DensityC; Voltage 25 V; MPN T521B226M025ATE100
C25, C26, C27, C33, C34: 100n; C_0402_1005Metric; Voltage 50 V; MPN GCM155R71H104KE02D
C28: 2.2µ; C_0603_1608Metric; Voltage 16 V; MPN GRM188R71C225KE15D
C29: 100n; C_0402_1005Metric_NoSilk; Voltage 50 V; MPN GCM155R71H104KE02D
C30, C31, C32: 22p; C_0402_1005Metric; Voltage 50 V; MPN GCM1555C1H220JA16D
R9, R11, R12: 3.3k; R_0402_1005Metric; MPN CRCW04023K30FKED
R10: 5.1k; R_0402_1005Metric; MPN CRCW04025K10FKED
R13: 3.3k; R_0402_1005Metric_NoSilk; MPN CRCW04023K30FKED
R14, R16: 100; R_0402_1005Metric_NoSilk; MPN CRCW0402100RFKED
R15: 100; R_0402_1005Metric; MPN CRCW0402100RFKED
R17, R18, R19: 330; R_0402_1005Metric; MPN CRCW0402330RFKED
R20, R21: 0.100 Ω; Vishay_WSL0603_1608Metric; Tolerance 1%; Rating 0.1 W; MPN WSL0603R1000FEA
U7: DRV8311PQRRWRQ1; Texas_RRW0024A_WQFN-24-1EP_3x3mm_P0.4mm_EP1.9x1.9mm; MPN DRV8311PQRRWRQ1
U8, U9: INA241A3QDDFRQ1; TI_DDF0008A_SOT-23-8_2.9x1.6mm_P0.65mm; MPN INA241A3QDDFRQ1

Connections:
+3V3: C29.1, C33.1, C34.1, R10.1, R11.1, R12.1, R13.1, U7.2 (CSAREF), U8.6 (VS), U8.7 (REF1), U9.6 (VS), U9.7 (REF1); also elsewhere on the board
/MOTOR_VM: C24.1, C25.1, C26.1, C27.1, U7.7 (VIN_AVDD), U7.8 (VM); also elsewhere on the board
/Motor control/DRV_CS_N: U7.20 (~SCS); also elsewhere on the board
/Motor control/DRV_FAULT_N: R10.2, U7.1 (~FAULT); also elsewhere on the board
/Motor control/DRV_SCLK: U7.23 (SCLK); also elsewhere on the board
/Motor control/DRV_SDI: U7.22 (SDI); also elsewhere on the board
/Motor control/DRV_SDO: U7.21 (SDO); also elsewhere on the board
/Motor control/DRV_SYNC: U7.19 (PWM_SYNC); also elsewhere on the board
/Motor control/DRV_WAKE: R9.1, U7.24 (~SLEEP); also elsewhere on the board
/Motor control/HALL_A: R14.2; also elsewhere on the board
/Motor control/HALL_B: R15.2; also elsewhere on the board
/Motor control/HALL_C: R16.2; also elsewhere on the board
/Motor control/ISENSE_A: C30.1, R17.2; also elsewhere on the board
/Motor control/ISENSE_B: C31.1, R18.2; also elsewhere on the board
/Motor control/ISENSE_C: C32.1, R19.2; also elsewhere on the board
/Three-phase bridge/CSA_C: R19.1, U7.3 (SOC)
/Three-phase bridge/DRV_AVDD: C28.1, U7.17 (AVDD)
/Three-phase bridge/DRV_CP: C27.2, U7.6 (CP)
/Three-phase bridge/HALL_RAW_A: R11.2, R14.1; also elsewhere on the board
/Three-phase bridge/HALL_RAW_B: R12.2, R15.1; also elsewhere on the board
/Three-phase bridge/HALL_RAW_C: R13.2, R16.1; also elsewhere on the board
/Three-phase bridge/PHASE_A: R20.2, U8.1 (IN−); also elsewhere on the board
/Three-phase bridge/PHASE_A_SW: R20.1, U7.10 (OUTA), U8.8 (IN+)
/Three-phase bridge/PHASE_B: R21.2, U9.1 (IN−); also elsewhere on the board
/Three-phase bridge/PHASE_B_SW: R21.1, U7.11 (OUTB), U9.8 (IN+)
/Three-phase bridge/PHASE_C: U7.12 (OUTC); also elsewhere on the board
GND: C24.2, C25.2, C26.2, C28.2, C29.2, C30.2, C31.2, C32.2, C33.2, C34.2, R9.2, U7.9 (PGND), U7.14 (AD1), U7.15 (AD0), U7.16 (AGND), U7.25 (EP), U8.2 (GND), U8.3 (REF2), U8.4 (NC), U9.2 (GND), U9.3 (REF2), U9.4 (NC); also elsewhere on the board
unnamed: R17.1, U8.5 (OUT)
unnamed: R18.1, U9.5 (OUT)

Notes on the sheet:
2610T012B motor drive
Phase B
Phase C low-side cross-check
Rotor Hall feedback
C25 to pin 8, C26 to pin 7.
3.3 V Hall supply and pull-ups (AN 163, Table 4).
Inline phase-current sensing
Phase A
tSPI address 0
3 mA gives 15 mV at the ADC input. Use Kelvin taps at each shunt.
